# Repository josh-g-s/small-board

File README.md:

# Board notes

- **Board outline bounding box:** 36.527 × 44.044 mm = **1608.80 mm²**. Single closed outline. Only the antenna section of the ESP32 module overhangs the top edge, as the rules allow; the module body is on the board.
- **Files:** `pcb_challenge_final.kicad_pcb`, `pcb_challenge_final.kicad_pro`, `pcb_challenge_final.kicad_dru` (KiCad 10 board, project and custom rules).

## Stack-up (1.6 mm FR4)
F.Cu signal + top parts / 0.1 prepreg / **In1.Cu GND** / 1.24 core / **In2.Cu +3.3V** / 0.1 prepreg / B.Cu signal + bottom parts.

The USB pair (D+/D−) runs on F.Cu only, with no vias. It sits entirely over one continuous In1 GND region, with no plane splits under it.

## Global rules (Board Setup → Constraints)
| Rule | Value |
|---|---|
| Track width | 0.15 mm |
| Clearance | 0.12 mm |
| Copper to board edge | 0.3 mm |
| Via drill | 0.3 mm |
| Via annular ring | 0.15 mm (0.6 mm vias) |
| Vias in pads | none |
| Flip-flop (XSON6) pad traces | 0.17 mm or less |

All vias are standard 0.3 mm / 0.6 mm through-hole vias (no blind, buried or micro vias). This keeps the board on a standard, low-cost 4-layer process: blind and buried vias need sequential lamination or depth-controlled drilling, which costs several times more, takes longer to make and adds failure points. It also keeps every via outside all IC courtyards on every layer.

## IC rule
- **As worded:** there are no vias inside any IC courtyard, and no other nets' traces inside an IC courtyard on that IC's own layer.
- **Stricter version we also follow:** no vias inside any IC courtyard on any layer.
- `pcb_challenge_final.kicad_dru` encodes these checks, so DRC enforces them.

## Readme issues 7 and 8 (applied ahead of the official board)
- **Issue 7:** Y2 pin 1 (oscillator EN) is connected to `en`.
- **Issue 8:** all four J3 shield (SH) pads are connected to Net-(J3-SHIELD) together with R6 and R24.

All named nets match the official board exactly; unused pins are left unconnected.

## DRC (KiCad 10.0.6, zones refilled)
- 0 unconnected items.
- The only errors are the known flip-flop `malformed_courtyard` errors from the provided XSON6 footprint.
- All footprints are the provided ones and are unmodified.
- The single ESP32 "footprint does not match library" warning comes from the 4-layer switch. The official board shows it too once set to 4 layers.
- The 27 "library not in configuration" warnings come from the embedded `reg`, `adder` and `3v3_ldo` footprints.
- **J3 hole clearance rule:** the unmodified library USB-C footprint puts pad B12 0.185 mm from its own NPTH locating peg. KiCad reports this intermittently as a hole-clearance error. `pcb_challenge_final.kicad_dru` relaxes hole clearance to 0.15 mm only between J3's own pad and hole pairs; everything else stays at 0.25 mm. If DRC is run without our rules file, this library item may appear intermittently.

## Silkscreen
Reference designators are hidden on the silkscreen, which the rules allow. Component outlines and polarity marks are kept.

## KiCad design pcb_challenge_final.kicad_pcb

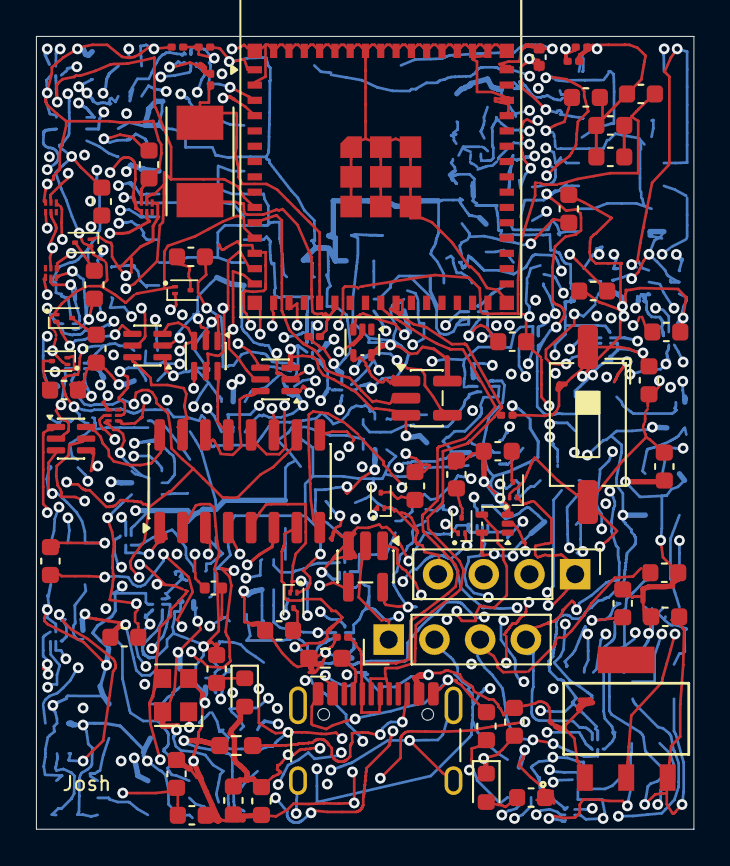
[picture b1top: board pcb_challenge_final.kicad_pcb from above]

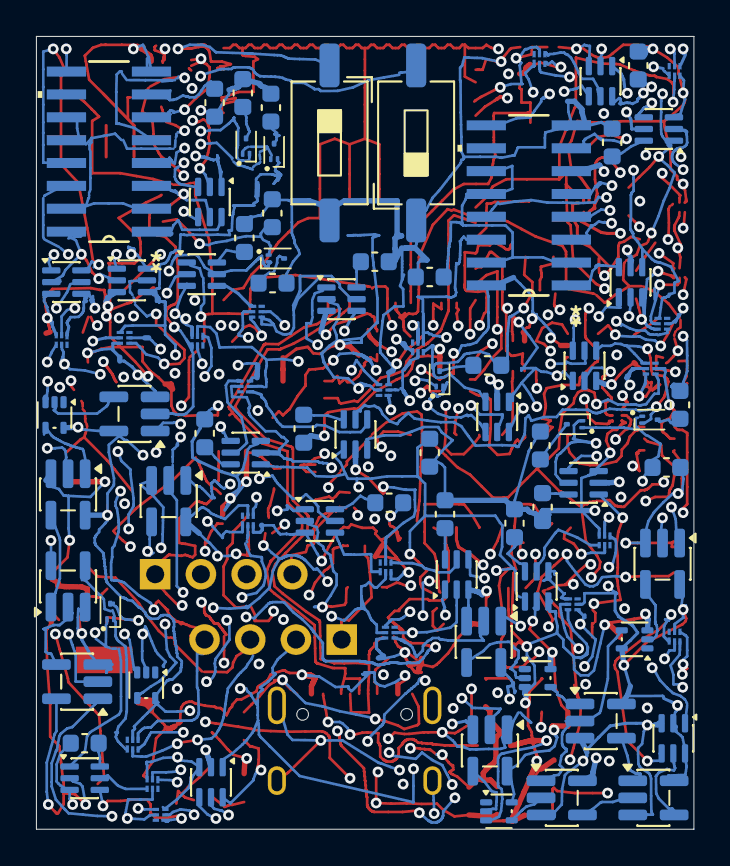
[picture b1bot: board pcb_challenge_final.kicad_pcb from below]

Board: 4 copper layers, 36.5 x 44.0 mm, 164 parts (88 on the bottom side), 134 nets.

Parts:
C1, C7: 22uF; C_0201_0603Metric
C2, C8: 0.1uF; C_0201_0603Metric
C3, C4: 12pF; C_0201_0603Metric
C5, C6: 22pF; C_0201_0603Metric
C9: 100nF; C_0402_1005Metric
C13, C14: 1uF; C_0603_1608Metric
C15, C20: 10uF; C_0603_1608Metric
D1: BLED; LED_0603_1608Metric
GREEN_LED1: LED; LED_0603_1608Metric
J3: USB_C_Receptacle_HCTL_HC-TYPE-C-16P-01A
J4, J5: Conn_01x04_Pin; PinHeader_1x04_P2.54mm_Vertical
Q15, Q16, Q17, Q18, Q19, Q20, Q21, Q22, Q23, Q24, Q25, Q26, Q27, Q28, Q29: Q_Dual_NPN_PNP_B1E2B2C2E1C1; SOT-1123
R1: 10k; C_0402_1005Metric
R3: 1k; C_0603_1608Metric
R4: 330; C_0603_1608Metric
R6, R24: 1M; C_0603_1608Metric
R7, R21, R22, R23, R25, R26, R27, R28, R29, R30, R31, R32, R33, R34, R35, R36, R37, R38, R39, R40, R41, R42, R43, R44, R45, R46, R47, R48, R49, R50, R51, R52, R53, R54, R55, R56, R57, R58, R59, R61, R62, R63, R64, R65, R66, R67, R68: 10k; C_0603_1608Metric
R15, R20: 5.1k; R_0603_1608Metric_Pad0.98x0.95mm_HandSolder
SW1, SW2, SW3: SW_Push; SW_DIP_SPSTx01_Slide_6.7x4.1mm_W8.61mm_P2.54mm_LowProfile
U1, U4, U5, U6, U7, U8, U17, U19, U20, U33, U34, U37, U38, U45, U46, U47, U48, U49, U50, U65, U66, U67, U68, U69: 74AUP1G80; XSON6_SOT1115_NEX
U3, U18, U52, U55, U56, U60: 74AHC1G86; SC-74A-5_1.55x2.9mm_P0.95mm
U9: TC1262-25; SOT-223_3MC_MCH
U10: NMUX1308BQ; SO-16_3.9x9.9mm_P1.27mm
U11, U12, U13, U14, U15, U16, U29, U30, U31, U32, U35, U36, U39, U40, U41, U42, U43, U44, U64, U70, U71, U72, U73: NMUX1308BQ; SOT-363_SC-70-6
U21, U23, U27, U51, U59, U62, U63: 74LV1T08GV; SC-74A-5_1.55x2.9mm_P0.95mm
U22, U28: CD74HC283M96; D16
U24, U26, U53, U54, U57, U58, U61: 74LVC1GU04DRL; SOT-553
U25: ESP32-S3-MINI-1; ESP32-S2-MINI-1
Y1: 32.768KHz; Crystal_SMD_Abracon_ABM7-2Pin_6.0x3.5mm
Y2: KC2520Z; Oscillator_SMD_Kyocera_KC2520Z-4Pin_2.5x2.0mm

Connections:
+3.3V: C1.1, C2.1, C14.1, R1.1, R3.1, U1.5 (VCC), U3.5 (VCC), U4.5 (VCC), U5.5 (VCC), U6.5 (VCC), U7.5 (VCC), U8.5 (VCC), U9.3 (VO), U10.1 (V_{CC}), U11.2 (V_{CC}), U12.2 (V_{CC}), U13.2 (V_{CC}), U14.2 (V_{CC}), U15.2 (V_{CC}), U16.2 (V_{CC}), U17.5 (VCC), U18.5 (VCC), U19.5 (VCC), U20.5 (VCC), U21.5 (VCC), U22.6 (B0), U22.16 (VCC), U23.5 (VCC), U24.5 (+), U25.3 (3V3), U26.5 (+), U27.5 (VCC), U28.6 (B0), U28.16 (VCC), U29.2 (V_{CC}), U30.2 (V_{CC}), U31.2 (V_{CC}), U32.2 (V_{CC}), U33.5 (VCC), U34.5 (VCC), U35.2 (V_{CC}), U36.2 (V_{CC}), U37.5 (VCC), U38.5 (VCC), U39.2 (V_{CC}), U40.2 (V_{CC}), U41.2 (V_{CC}), U42.2 (V_{CC}), U43.2 (V_{CC}), U44.2 (V_{CC}), U45.5 (VCC), U46.5 (VCC), U47.5 (VCC), U48.5 (VCC), U49.5 (VCC), U50.5 (VCC), U51.5 (VCC), U52.5 (VCC), U53.5 (+), U54.5 (+), U55.5 (VCC), U56.5 (VCC), U57.5 (+), U58.5 (+), U59.5 (VCC), U60.5 (VCC), U61.5 (+), U62.5 (VCC), U63.5 (VCC), U64.2 (V_{CC}), U64.6 (Y1), U65.5 (VCC), U66.5 (VCC), U67.5 (VCC), U68.5 (VCC), U69.5 (VCC), U70.2 (V_{CC}), U71.2 (V_{CC}), U72.2 (V_{CC}), U73.2 (V_{CC}), Y2.4 (VCC)
+5V: C13.1, C15.1, C20.1, GREEN_LED1.2 (A), J3.A4 (VBUS), J3.A9 (VBUS), J3.B4 (VBUS), J3.B9 (VBUS), U9.1 (VI)
???: J5.4, U1.4 (~Q), U26.2
COUT: U22.9 (COUT), U28.9 (COUT)
GND: C1.2, C2.2, C3.1, C4.1, C5.2, C6.2, C7.2, C8.2, C9.2, C13.2, C14.2, C15.2, C20.2, D1.1 (K), J3.A1 (GND), J3.A12 (GND), J3.B1 (GND), J3.B12 (GND), R4.1, R6.1, R7.1, R15.1, R20.2, R21.1, R22.1, R23.1, R24.1, R25.1, R26.1, R27.1, R28.1, R29.1, R30.1, R31.1, R32.1, R33.1, R34.1, R35.1, R36.1, R37.1, R38.1, R39.1, R40.1, R41.1, R42.1, R43.1, R44.1, R45.1, R46.1, R47.1, R48.1, R49.1, R50.1, R51.1, R52.1, R53.1, R54.1, R55.1, R56.1, R57.1, R58.1, R59.1, R61.1, R62.1, R63.1, R64.1, R65.1, R66.1, R67.1, R68.1, SW1.1, SW2.1, SW3.2, U1.3 (GND), U3.3 (GND), U4.3 (GND), U5.3 (GND), U6.3 (GND), U7.3 (GND), U8.3 (GND), U9.2 (GND), U10.2 (GND), U11.3 (GND), U12.3 (GND), U13.3 (GND), U14.3 (GND), U15.3 (GND), U16.3 (GND), U17.3 (GND), U18.3 (GND), U19.3 (GND), U20.3 (GND), U21.3 (GND), U22.8 (GND), U23.3 (GND), U24.3 (-), U25.1 (GND), U26.3 (-), U27.3 (GND), U28.8 (GND), U29.3 (GND), U30.3 (GND), U31.3 (GND), U32.3 (GND), U33.3 (GND), U34.3 (GND), U35.3 (GND), U36.3 (GND), U37.3 (GND), U38.3 (GND), U39.3 (GND), U40.3 (GND), U41.3 (GND), U42.3 (GND), U43.3 (GND), U44.3 (GND), U45.3 (GND), U46.3 (GND), U47.3 (GND), U48.3 (GND), U49.3 (GND), U50.3 (GND), U51.3 (GND), U52.3 (GND), U53.3 (-), U54.3 (-), U55.3 (GND), U56.3 (GND), U57.3 (-), U58.3 (-), U59.3 (GND), U60.3 (GND), U61.3 (-), U62.3 (GND), U63.3 (GND), U64.3 (GND), U65.3 (GND), U66.3 (GND), U67.3 (GND), U68.3 (GND), U69.3 (GND), U70.3 (GND), U71.3 (GND), U72.3 (GND), U73.3 (GND), Y2.2 (GND)
IO6: U6.2 (C), U7.2 (C), U8.2 (C), U25.10 (IO6), U45.2 (C), U46.2 (C), U47.2 (C), U48.2 (C), U49.2 (C), U50.2 (C), U65.2 (C), U66.2 (C), U67.2 (C), U68.2 (C), U69.2 (C)
IO7: U21.2 (A), U25.11 (IO7)
IO8: Q18.1 (B1), Q19.1 (B1), Q20.1 (B1), Q24.1 (B1), Q25.1 (B1), Q26.1 (B1), Q27.1 (B1), R35.2, R37.2, R39.2, R61.2, R63.2, R65.2, R67.2, U25.12 (IO8), U39.1 (S0), U40.1 (S0), U41.1 (S0), U42.1 (S0), U43.1 (S0), U44.1 (S0), U64.1 (S0)
IO9: U24.2, U25.13 (IO9), U65.4 (~Q)
IO10: U25.14 (IO10), U69.4 (~Q), U73.5 (Y0)
IO11: U25.15 (IO11), U68.4 (~Q), U70.5 (Y0)
IO12: U25.16 (IO12), U67.4 (~Q), U71.5 (Y0)
IO13: U25.17 (IO13), U66.4 (~Q), U72.5 (Y0)
unnamed: D1.2 (A), R3.2
unnamed: GREEN_LED1.1 (K), R4.2
unnamed: J3.A5 (CC1), R20.1
unnamed: J3.B5 (CC2), R15.2
unnamed: J3.SH, R6.2, R24.2
unnamed: Q15.3 (E1), R30.2
unnamed: Q16.2 (C1), U1.1 (D), U27.4 (Y)
unnamed: Q16.3 (E1), R32.2
unnamed: Q17.3 (E1), R28.2
unnamed: Q18.3 (E1), R40.2
unnamed: Q19.3 (E1), R38.2
unnamed: Q20.3 (E1), R36.2
unnamed: Q21.3 (E1), R44.2
unnamed: Q22.3 (E1), R45.2
unnamed: Q23.3 (E1), R46.2
unnamed: Q24.2 (C1), U66.1 (D), U72.4 (Out)
unnamed: Q24.3 (E1), R62.2
unnamed: Q25.2 (C1), U67.1 (D), U71.4 (Out)
unnamed: Q25.3 (E1), R64.2
unnamed: Q26.2 (C1), U68.1 (D), U70.4 (Out)
unnamed: Q26.3 (E1), R66.2
unnamed: Q27.2 (C1), U69.1 (D), U73.4 (Out)
unnamed: Q27.3 (E1), R68.2
unnamed: Q28.3 (E1), R26.2
unnamed: Q29.3 (E1), R22.2
unnamed: U18.4, U54.2
unnamed: U21.1 (B), U24.4
unnamed: R33.2, U22.2 (B1), U22.11 (B3), U22.12 (A3), U22.15 (B2)
unnamed: R25.2, U22.7 (CIN)
unnamed: U23.1 (B), U26.4
unnamed: C7.1, C8.1, R1.2, SW3.1, U25.45 (EN)
unnamed: U25.2 (GND), U25.42 (GND), U25.43 (GND), U25.46 (GND), U25.47 (GND), U25.48 (GND), U25.49 (GND), U25.50 (GND), U25.51 (GND), U25.52 (GND), U25.53 (GND), U25.54 (GND), U25.55 (GND), U25.56 (GND), U25.57 (GND), U25.58 (GND), U25.59 (GND), U25.60 (GND), U25.61 (GND), U25.62 (GND), U25.63 (GND), U25.64 (GND), U25.65 (GND)
unnamed: SW1.2, U25.4 (IO0)
unnamed: C3.2, U25.19 (IO15), Y1.2
unnamed: C4.2, U25.20 (IO16), Y1.1
unnamed: U3.4, U27.2 (A)
unnamed: U27.1 (B), U51.4 (Y)
unnamed: R47.2, U28.2 (B1), U28.11 (B3), U28.12 (A3), U28.15 (B2)
unnamed: R34.2, U28.7 (CIN)
unnamed: U4.1 (D), U29.4 (Out)
unnamed: R48.2, U29.6 (Y1)
unnamed: U5.1 (D), U30.4 (Out)
unnamed: U4.4 (~Q), U30.5 (Y0)
unnamed: R49.2, U30.6 (Y1)
unnamed: U31.4 (Out), U33.1 (D)
unnamed: R50.2, U31.6 (Y1)
unnamed: U32.4 (Out), U34.1 (D)
unnamed: U32.5 (Y0), U33.4 (~Q)
unnamed: R51.2, U32.6 (Y1)
unnamed: U35.4 (Out), U37.1 (D)
unnamed: R52.2, U35.6 (Y1)
unnamed: U36.4 (Out), U38.1 (D)
unnamed: U36.5 (Y0), U37.4 (~Q)
unnamed: R53.2, U36.6 (Y1)
unnamed: U39.4 (Out), U45.1 (D)
unnamed: R54.2, U39.6 (Y1)
unnamed: U40.4 (Out), U46.1 (D)
unnamed: R55.2, U40.6 (Y1)
unnamed: U41.4 (Out), U47.1 (D)
unnamed: R56.2, U41.6 (Y1)
unnamed: U42.4 (Out), U48.1 (D)
unnamed: U42.5 (Y0), U45.4 (~Q)
unnamed: R57.2, U42.6 (Y1)
unnamed: U43.4 (Out), U49.1 (D)
unnamed: U43.5 (Y0), U46.4 (~Q)
unnamed: R58.2, U43.6 (Y1)
unnamed: U44.4 (Out), U50.1 (D)
unnamed: U44.5 (Y0), U47.4 (~Q)
unnamed: R59.2, U44.6 (Y1)
unnamed: U51.2 (A), U54.4
unnamed: U51.1 (B), U53.4
unnamed: U52.4, U53.2
unnamed: U55.4, U57.2
unnamed: U56.4, U58.2
unnamed: U57.4, U59.2 (A)
unnamed: U58.4, U59.1 (B), U62.2 (A)
unnamed: U59.4 (Y), U63.2 (A)
unnamed: U60.4, U61.2
unnamed: U61.4, U62.1 (B)
unnamed: U62.4 (Y), U63.1 (B)
unnamed: U63.4 (Y), U64.5 (Y0)
unnamed: U64.4 (Out), U65.1 (D)
R_en: U10.12 (EN), U14.1 (S0), U15.1 (S0), U16.1 (S0), U23.4 (Y)
USB_D+: C5.1, J3.A6 (D+), J3.B6 (D+), U25.24 (USB_D+)
USB_D-: C6.1, J3.A7 (D-), J3.B7 (D-), U25.23 (USB_D-)
b1: J4.4, Q29.2 (C1), U10.4 (in1)
b2: J4.3, Q28.2 (C1), U10.5 (in2)
b3: J4.2, Q17.2 (C1), U10.6 (in3)
b4: J4.1, Q15.2 (C1), U10.7 (in4)
clk: J5.3, R7.2, U1.2 (C), U4.2 (C), U5.2 (C), U10.3 (clk), U17.2 (C), U19.2 (C), U20.2 (C), U33.2 (C), U34.2 (C), U37.2 (C), U38.2 (C), Y2.3 (CLK)
en: J5.1, U23.2 (A), Y2.1 (INH)
out_1: U10.13 (o1), U73.6 (Y1)
out_2: U10.14 (o2), U70.6 (Y1)
out_3: U10.15 (o3), U71.6 (Y1)
out_4: U10.16 (o4), U72.6 (Y1)
r_en: U11.1 (S0), U12.1 (S0), U13.1 (S0), U21.4 (Y), U70.1 (S0), U71.1 (S0), U72.1 (S0), U73.1 (S0)
rc1: U7.4 (~Q), U10.10 (in1), U12.5 (Y0), U22.5 (A0), U60.1
rc2: U6.4 (~Q), U10.11 (in2), U11.5 (Y0), U22.3 (A1), U56.2
rc3: U8.4 (~Q), U13.5 (Y0), U22.14 (A2), U55.2
reg1: U5.4 (~Q), U18.1
reg2: U34.4 (~Q), U52.1
reg3: U3.1, U38.4 (~Q)
rs0: U12.6 (Y1), U22.4 (S0)
rs1: U11.6 (Y1), U22.1 (S1)
rs2: U13.6 (Y1), U22.13 (S2)
rst: C9.1, J5.2, Q15.1 (B1), Q16.1 (B1), Q17.1 (B1), Q21.1 (B1), Q22.1 (B1), Q23.1 (B1), Q28.1 (B1), Q29.1 (B1), R21.2, R23.2, R27.2, R29.2, R31.2, R41.2, R42.2, R43.2, SW2.2, U29.1 (S0), U30.1 (S0), U31.1 (S0), U32.1 (S0), U35.1 (S0), U36.1 (S0)
rw1: Q20.2 (C1), U7.1 (D), U12.4 (Out), U29.5 (Y0)
rw2: Q19.2 (C1), U6.1 (D), U11.4 (Out), U31.5 (Y0)
rw3: Q18.2 (C1), U8.1 (D), U13.4 (Out), U35.5 (Y0)
wc1: U10.8 (in1), U15.5 (Y0), U18.2, U20.4 (~Q), U28.5 (A0)
wc2: U10.9 (in2), U14.5 (Y0), U19.4 (~Q), U28.3 (A1), U52.2
wc3: U3.2, U16.5 (Y0), U17.4 (~Q), U28.14 (A2)
wir1: U48.4 (~Q), U60.2
wir2: U49.4 (~Q), U56.1
wir3: U50.4 (~Q), U55.1
wr1: Q23.2 (C1), U15.4 (Out), U20.1 (D), U39.5 (Y0)
wr2: Q22.2 (C1), U14.4 (Out), U19.1 (D), U40.5 (Y0)
wr3: Q21.2 (C1), U16.4 (Out), U17.1 (D), U41.5 (Y0)
ws0: U15.6 (Y1), U28.4 (S0)
ws1: U14.6 (Y1), U28.1 (S1)
ws2: U16.6 (Y1), U28.13 (S2)
